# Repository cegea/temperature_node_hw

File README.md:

# Temperature node
PCB design for a temperature sensor based on SHT and ESP32.

#  Requirement Specifications

- Battery Operated: The node should operate on a battery with a lifespan of over a month.
- WiFi Connection: Supports 2.4 GHz WiFi to connect to a home network.
- MQTT Protocol: Publishes temperature and humidity data to an MQTT broker.
- Compact Design: Designed for easy placement in various locations around the home.
- Temperature and Humidity Reporting: Uses an SHT series sensor for accurate measurements.

# Functional Requirements Specification
## Electrical

- Battery Life: Should last more than a month on a single charge.
- Power Consumption: Optimized deep-sleep mode for low power consumption between readings.
- Input Voltage: 3.3V for ESP32 and 3V to 5V compatible for SHT sensors.
- Charging: Option for USB-C charging or solar panel for extended battery life.
- Voltage Regulation: Include a voltage regulator to ensure stable power delivery to ESP32 and the sensor.

## Mechanical

- Enclosure: IP65-rated enclosure for dust and water resistance if placed in areas prone to moisture.
- Size: Compact size, around 5cm x 5cm x 3cm, to fit easily on shelves or mounted on walls.
- Mounting (Optional): Option for wall mounting with screw holes or adhesive backing.
- Internal Antenna: PCB antenna for better WiFi range within the home.
- Access Ports: A small access port for USB charging and maintenance.

## Functional

- Data Reporting Interval: Configurable reporting interval (e.g., every 5 minutes, 10 minutes) to balance battery life and data frequency.
- Low Battery Alert: Sends an MQTT message when the battery level falls below a certain threshold.
- Temperature Range: Measures temperature from -20°C to +60°C.
- Humidity Range: Measures humidity from 0% to 100% relative humidity.
- OTA Updates: Supports Over-the-Air (OTA) firmware updates to improve functionality without physical access.
- Reconnection Logic: Automatically attempts to reconnect to WiFi and MQTT broker in case of network loss.
- Local Data Storage: Stores data temporarily in case of WiFi disconnection and uploads when the connection is restored.

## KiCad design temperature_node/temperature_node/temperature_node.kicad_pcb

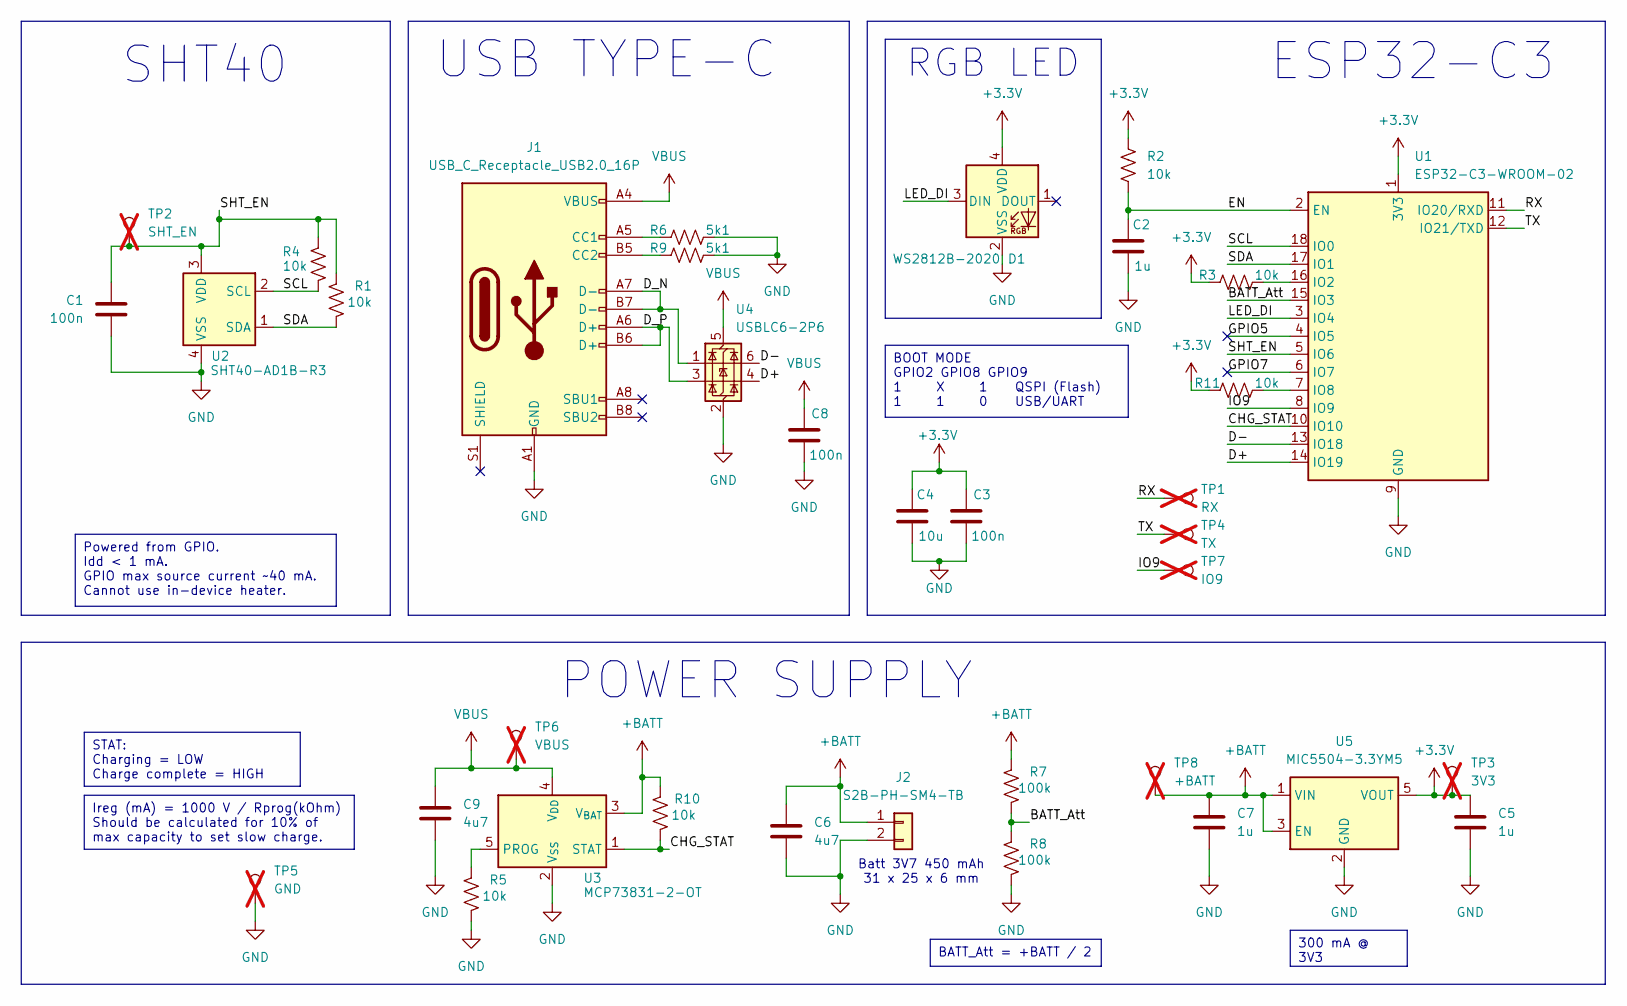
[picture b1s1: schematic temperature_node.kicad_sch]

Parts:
C1, C3, C8: 100n; C_0402_1005Metric; LCSC PN C60474
C2, C5, C7: 1u; C_0402_1005Metric; LCSC PN C60474
C4: 10u; C_0805_2012Metric; LCSC PN C17024
C6, C9: 4u7; C_0603_1608Metric; LCSC PN C913474
D1: WS2812B-2020; LED_WS2812B-2020_PLCC4_2.0x2.0mm; LCSC PN C965555
J1: USB_C_Receptacle_USB2.0_16P; USB_C_Receptacle_GCT_USB4110; LCSC PN C5143397
J2: S2B-PH-SM4-TB; JST_PH_S2B-PH-SM4-TB_1x02-1MP_P2.00mm_Horizontal; LCSC PN C295747
R1, R2, R3, R4, R5, R10, R11: 10k; R_0402_1005Metric; LCSC PN C723366
R6, R9: 5k1; R_0402_1005Metric; LCSC PN C25905
R7, R8: 100k; R_0402_1005Metric; LCSC PN C102760
TP1: RX; TestPoint_Pad_D1.0mm; not fitted
TP2: SHT_EN; TestPoint_Pad_D1.0mm; not fitted
TP3: 3V3; TestPoint_Pad_D1.0mm; not fitted
TP4: TX; TestPoint_Pad_D1.0mm; not fitted
TP5: GND; TestPoint_Pad_D1.0mm; not fitted
TP6: VBUS; TestPoint_Pad_D1.0mm; not fitted
TP7: IO9; TestPoint_Pad_D1.0mm; not fitted
TP8: +BATT; TestPoint_Pad_D1.0mm; not fitted
U1: ESP32-C3-WROOM-02; LCSC PN C2934560
U2: SHT40-AD1B-R3; Sensirion_DFN-4_1.5x1.5mm_P0.8mm_SHT4x_NoCentralPad
U3: MCP73831-2-OT; SOT-23-5; LCSC PN C150772
U4: USBLC6-2P6; SOT-666; LCSC PN C2827693
U5: MIC5504-3.3YM5; SOT-23-5; LCSC PN C3021093

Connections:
+3.3V: C3.1, C4.1, C5.1, D1.4 (VDD), R2.1, R3.2, R11.2, TP3.1, U1.1 (3V3), U5.5 (VOUT)
+BATT: C6.1, C7.1, J2.1, R7.1, R10.1, TP8.1, U3.3 (V_{BAT}), U5.1 (VIN), U5.3 (EN); also elsewhere on the board
/BATT_Att: R7.2, R8.1, U1.15 (IO3)
/CHG_STAT: R10.2, U1.10 (IO10), U3.1 (STAT)
/D+: U1.14 (IO19), U4.4 (I/O2)
/D-: U1.13 (IO18), U4.6 (I/O1)
/D_N: J1.A7 (D-), J1.B7 (D-), U4.1 (I/O1); also elsewhere on the board
/D_P: J1.A6 (D+), J1.B6 (D+), U4.3 (I/O2); also elsewhere on the board
/EN: C2.1, R2.2, U1.2 (EN)
/GPIO5: U1.4 (IO5)
/GPIO7: U1.6 (IO7)
/IO9: TP7.1, U1.8 (IO9)
/LED_DI: D1.3 (DIN), U1.3 (IO4)
/RX: TP1.1, U1.11 (IO20/RXD)
/SCL: R4.2, U1.18 (IO0), U2.2 (SCL)
/SDA: R1.2, U1.17 (IO1), U2.1 (SDA)
/SHT_EN: C1.1, R1.1, R4.1, TP2.1, U1.5 (IO6), U2.3 (VDD)
/TX: TP4.1, U1.12 (IO21/TXD)
GND: C1.2, C2.2, C3.2, C4.2, C5.2, C6.2, C7.2, C8.2, C9.2, D1.2 (VSS), J1.A1 (GND), J1.A12 (GND), J1.B1 (GND), J1.B12 (GND), J2.2, R5.2, R6.1, R8.2, R9.1, TP5.1, U1.9 (GND), U1.19 (GND), U2.4 (VSS), U3.2 (V_{SS}), U4.2 (GND), U5.2 (GND); also elsewhere on the board
unnamed 19: J1.A5 (CC1), R6.2; also elsewhere on the board
unnamed 20: J1.B5 (CC2), R9.2; also elsewhere on the board
unnamed: R3.1, U1.16 (IO2)
unnamed: R11.1, U1.7 (IO8)
unnamed: R5.1, U3.5 (PROG)
VBUS: C8.1, C9.1, J1.A4 (VBUS), J1.A9 (VBUS), J1.B4 (VBUS), J1.B9 (VBUS), TP6.1, U3.4 (V_{DD}), U4.5 (VBUS); also elsewhere on the board

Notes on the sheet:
Powered from GPIO. Idd < 1 mA. GPIO max source current ~40 mA. Cannot use in-device heater.
Ireg (mA) = 1000 V / Rprog(kOhm) Should be calculated for 10% of max capacity to set slow charge.
300 mA @ 3V3
BOOT MODE GPIO2 GPIO8 GPIO9 1 X 1 QSPI (Flash) 1 1 0 USB/UART
STAT: Charging = LOW Charge complete = HIGH
BATT_Att = +BATT / 2
SHT40
${TITLE}
POWER SUPPLY
Batt 3V7 450 mAh 31 x 25 x 6 mm
ESP32-C3
RGB LED
USB TYPE-C

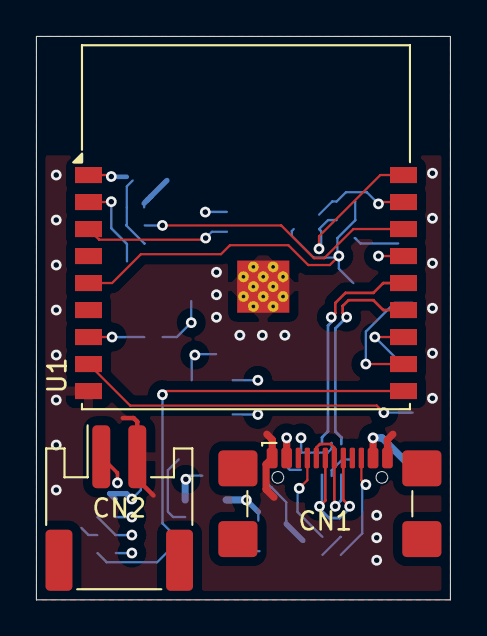
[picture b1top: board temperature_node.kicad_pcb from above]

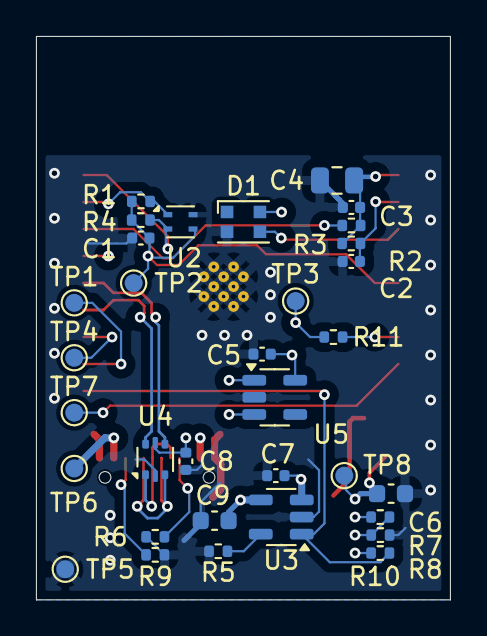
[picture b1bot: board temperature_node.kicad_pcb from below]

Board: 4 copper layers, 23.0 x 31.3 mm, 36 parts (33 on the bottom side), 23 nets.

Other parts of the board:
CN1: USB_C_Receptacle_USB2.0_16P; USB_C_Receptacle_GCT_USB4110
CN2: S2B-PH-SM4-TB; JST_PH_S2B-PH-SM4-TB_1x02-1MP_P2.00mm_Horizontal

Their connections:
+BATT: CN2.1; also elsewhere on the board
/D_N: CN1.A7 (D-), CN1.B7 (D-); also elsewhere on the board
/D_P: CN1.A6 (D+), CN1.B6 (D+); also elsewhere on the board
GND: CN1.A1 (GND), CN1.A12 (GND), CN1.B1 (GND), CN1.B12 (GND), CN2.2; also elsewhere on the board
unnamed 19: CN1.A5 (CC1); also elsewhere on the board
unnamed 20: CN1.B5 (CC2); also elsewhere on the board
VBUS: CN1.A4 (VBUS), CN1.A9 (VBUS), CN1.B4 (VBUS), CN1.B9 (VBUS); also elsewhere on the board

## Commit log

2024-10-18 Add specification and requirements
2024-10-18 Initial component selection and ESP32 peripherals
2024-10-19 Add esp32 module
2024-10-19 Connect USB and SHT40
2024-10-20 Finish pre stock review schematics
2024-10-30 Add datasheets to folder in repo.
2024-10-30 Add notes to SCH and review pre PCB design
2024-10-30 Set slow charge to 100 mA with RPROG as 10k
2024-10-31 Use a smaller header for UART connector
2024-10-31 Initial PCB component placement
2024-11-02 Add 1mm PAD test points
2024-11-02 Add GND test point and rearrange some nodes
2024-11-02 Preliminar placement
2024-11-03 Import JLCPCB DRC
2024-11-03 Re-placement to make the PCB smaller
2024-11-04 Change battery connector to SMD
2024-11-04 Continue making the board smaller
2024-11-04 Change USB C to SMD
2024-11-04 Add RX/TX nets
2024-11-04 Castellation pins for programming and resize for smaller board
2024-11-04 Reposition connectors
2024-11-05 Reposition some componentents and silkscreen
2024-11-05 Replace 5x5 mm RGB Led for a 2x2 mm
2024-11-05 Replace TVS Diode with a smaller ESD + TVS protection for USB. Add datasheets
2024-11-05 Add decoupling capacitor at VBUS for ESD protection
2024-11-05 Placement pre routing
2024-11-10 Add nets on both sides of the ESD proteciton
2024-11-10 Reorder connectors to shorter USB routing
2024-11-10 Replace pad with side connector for programming enable
2024-11-10 PCB Routed pre DRC
2024-11-11 Change "min_hole_clearance": 0.127,
2024-11-11 Move board edge
2024-11-14 Remove some DRC warnings
2024-11-15 Constellation pads added property for DRC
2024-11-15 Modify minimum hole size
2024-11-18 Replace header connector with testpoint
2024-11-18 Apply sch changes
2024-11-18 Add note for battery and fix wrong reference for battery connector
2024-11-18 PCB DRC Ok
2024-11-18 Reanotate PCB and SCH
2024-11-18 Add parameter for BOM and change some cap sizes for better availability
2024-11-18 update PCB with changed footprints
2024-11-18 Mod F.silkscreen
